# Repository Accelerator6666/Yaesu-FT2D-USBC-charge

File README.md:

# FT2D USB-C PD 外接电源适配器（工程评审版）

为 Yaesu FT2DR / FT2DE 手持电台设计的 USB-C PD 转外接直流电源原型工程，使用 KiCad 10。**本工程尚未完成量产前的电气、PCB 和实物验证，请勿直接投板后连接电台。**

## 优先推进：Rev P 低成本模块＋洞洞板路线（2026-10-26）

由于嘉立创 SMT 报价较高，现新增**不依赖 PCB 打板和 SMT 代贴**的 [Rev P 模块／洞洞板试验方案](prototypes/Rev_P_Perfboard/README.md)。用户提供的 **TA3005U 产品参数截图**显示 C1/C2 支持 **12 V / 3 A**，故**优先使用 12 V PD 直通方案**，无需降压模块：参见 [采购与装配清单](prototypes/Rev_P_Perfboard/PROCUREMENT_REV_PD.md)、[12 V 直通接线图](prototypes/Rev_P_Perfboard/wiring_12v_direct.svg) 和 [直通台架放行清单](prototypes/Rev_P_Perfboard/TEST_PLAN_12V_DIRECT.md)。原 [20 V→12 V 降压备选接线图](prototypes/Rev_P_Perfboard/wiring.svg) 与 [测试方案](prototypes/Rev_P_Perfboard/TEST_PLAN.md) 保留以备直通 3 A 动态能力不足时使用。两条路径均需**独立 OVP、保险丝及 E-DC-6 极性核对**。**当前仅完成设计和规格截图核对，尚未购买和实测，严禁直接接电台。**

Rev B 作为后续小型化 PCB 参考版本原样保留；此前嘉立创 **5 片 PCB 待付款订单**不受本次设计文件影响，本项目没有操作付款或撤单。

**最新进展（2026-10-26）：** [PCB Rev B 工作版](hardware/Rev_B/README.md) 已更换 J1 为 HRO `TYPE-C-31-M-12`（JLC **C165948**）、L1 为 JIERR `SRG1260-100-M`（**C53463013**），并完成接地回流修复、局部 1.6–2.0 mm 目标功率铜皮、重新填铜。C18 已采用 Panasonic `EEH-ZA1V470P`（**C178639**）的匹配 6.3 mm 焊盘作为候选，取代原 5 mm 焊盘型号，仍须核定温度等级。**本轮 U3 新增 4 颗标准功率过孔和 In2 两个独立局部宽铜岛；C26 从 100 nF 升级为 2.2 µF/25 V X7R 候选（C415535），0603 焊盘不变。** 更新后 KiCad 10.0.7 **ERC 0 / DRC 违规 0 / 未连接 0 / 原理图对照 0**，3 A 温升仍未签核。

嘉立创用的 [BOM/CPL 原生导出及 SMT 供料评审](manufacturing/Rev_B/README.md) 已更新到 **57 行原生 BOM / 53 个实际 SMT 坐标 / 53 个候选 JLC 物料号（37 种料）**；候选 JLC 四列 BOM、五列 CPL 与逐项来源追溯表都在 `REVIEW_ONLY_NOT_FOR_FAB`，并已通过 53/53 本地 BOM/CPL 位号和坐标审计。**R22 已由 101 kΩ 兼容改值为 102 kΩ（JLC SMT C861068），OVLO 标称值相应提高约 0.12 V，工厂实时库存仍需确认。4 层 Gerber、焊膏、钻孔已随本轮源工程重新导出。** 另新增 [嘉立创报价/贴片在线预览三件套](manufacturing/Rev_B/QUOTE_PREVIEW_ONLY_NOT_RELEASED/README_FIRST.md)：平铺 Gerber+钻孔 ZIP、53 位号 BOM 和 CPL，可以立即上传**预览/询价**，仍不能直接确认订单。同步生成了 [U3 3A 铜线保守损耗估算](manufacturing/Rev_B/PREFLIGHT/power_path_screening.json) 和 [STUSB4500 NVM/首板上电方案](manufacturing/Rev_B/PD_NVM_AND_FIRST_POWER_ON_PLAN.md)。尤其注意 STUSB4500 **出厂 20V PDO 只有 1A，且默认 5V 时可使能电源路径**，必须在首板测试前重新配置并验证。**当前仍 NO-GO，不要直接下单**：待完成 3 A 电热及 Buck 回路复核、全部候选元件真实 SMT 供货/兼容性确认、JLC 贴片预览和工程签核。正式放行脚本继续拦截未签核订单；原始评审 PCB 的 [基线检查](FAB_READINESS.md) 保留。

## 原 Rev B 集成 PCB 的目标参数（不适用于 Rev P-D 直通版）

| 项目 | 规格 |
| --- | --- |
| 输入 | USB-C PD 固定 20 V / ≥3 A（至少 60 W） |
| 输出 | 标称 12.5 V / 连续 3 A（37.5 W） |
| 设备端 | Yaesu E-DC-6 兼容尾线，使用前必须核对极性和尺寸 |
| 主控制器 | STUSB4500QTR（PD 协商）、LM61460-Q1（同步降压）、TPS259474A（eFuse） |
| PCB | 四层，含初始原型布局与自动布线评审版 |

FT2D 的电池充电由电台内部管理；此工程**不是**独立的锂电池充电器。

## 文件索引

- `FT2D_PD20V_12V5_3A_评审原理图.kicad_sch`：KiCad 原理图。
- `FT2D_PD20V_12V5_3A_评审原理图.kicad_pcb`：已导入自动布线的评审 PCB。
- `FT2D_PD20V_12V5_3A_原型板.kicad_pcb`：早期原型板布局版本。
- 两份 `.kicad_pro`：各自的工程设置；`.kicad_prl` 属于本地用户界面状态，没有纳入版本控制。
- `FT2D.kicad_sym`、`FT2D.pretty/`、`sym-lib-table`、`fp-lib-table`：自定义符号和封装库。
- `FT2D_PD20V_12V5_3A_BOM.csv`：元件清单。
- `FT2D_PD20V_12V5_3A_评审原理图.pdf`、`FT2D_PD20V_12V5_3A_评审.net`：评审导出资料。
- `FT2D_USB-C_PD_3A_设计说明.md`、`FT2D_PD20V_12V5_3A_原理图连接表.md`：设计要求、连接表及测试计划。
- `FT2D_PD20V_12V5_3A_ERC.txt`：提供的 ERC 检查记录（0 errors / 0 warnings；不能替代板级验证）。
- `generate_schematic.py`、`generate_pcb.py`、`make_footprints.py`、`postprocess_route.py`：设计辅助脚本。

## 打开方式

1. 安装 KiCad 10，下载或克隆本仓库。
2. **当前工作版**：打开 `hardware/Rev_B/FT2D_PD20V_12V5_3A_评审原理图.kicad_pro`，对应 `.kicad_sch` 和 `.kicad_pcb`；原始根目录文件保留为此前的评审基线。
3. `hardware/Rev_B/README.md` 有当前实际检查结果；`manufacturing/Rev_B/` 有不可投板的供料/CPL 预览与放行门禁。
4. 如需重新生成自定义封装，运行 `python make_footprints.py`。仓库已包含脚本生成的七个自定义封装。

部分其他自动生成脚本含有原开发环境的本地路径以及未附带的临时网络表输入，**不是**开箱即用的跨平台构建流程；直接阅读和编辑现有 KiCad 文件不依赖运行这些脚本。

## 投板与上机前必须确认

- 按厂家数据手册复核所有芯片、USB-C 连接器及自定义封装的引脚、焊盘和焊膏开窗。
- 重新运行 ERC / DRC、检查所有连接与四层铜皮，审查 Gerber / 钻孔。
- **Rev B 虽已有 1.6–2.0 mm 目标宽度的局部功率铜皮，但受限处仍有 0.3–0.6 mm 细颈，不等于全路径可连续承载 3 A。**需要完成电流通道截面、过孔与温升签核。
- 正确烧录、读回并验证 STUSB4500 NVM 的 PD 请求参数，确认非 20 V / 3 A 电源不会向电台供电。
- 不接 FT2D，先用电子负载验证输出电压、纹波、温升、负载阶跃、短路、过流、过压以及射频噪声影响。
- 实测电台端插头的正负极、机械匹配与满载电压后，才考虑连接真机。

更完整的参数和验收流程参见两份中文设计说明文档。当前工程没有提供足以证明安全可投板或已完成实测的资料。

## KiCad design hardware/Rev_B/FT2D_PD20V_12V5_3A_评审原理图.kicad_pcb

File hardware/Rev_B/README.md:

# FT2D PCB Rev B（JLCPCB 首板工作版，未放行）

检查日期：2026-10-26；KiCad 10.0.7；目标板厂：嘉立创 JLCPCB；目标工艺：4 层 PCB + SMT 代贴片。

> **规则检查已清零，但制造仍 NO-GO。** 本目录可在 KiCad 10 打开；J1/L1 换料、C18 新候选的焊盘调整、GND 回流布线、局部功率铜、U3 四颗标准过孔及 In2 两个局部功率铜岛均已同步，全部 DRC/Parity 通过。**53/53 个 SMT 位号已匹配候选 LCSC 编码，37 种物料均未正式获批**。剩余 3 A 功率/散热审查、JLC 实际供料/兼容性、元器件和装配方向签核尚不能省略。

## 当前可复现检查

```sh
kicad-cli sch erc --format json -o erc_rev_b.json FT2D_PD20V_12V5_3A_评审原理图.kicad_sch
kicad-cli pcb drc --schematic-parity --refill-zones --format json -o drc_rev_b.json FT2D_PD20V_12V5_3A_评审原理图.kicad_pcb
```

| 检查 | 实际结果 | 说明 |
| --- | --- | --- |
| 原理图 ERC | **0** | 仅表示静态 ERC 通过 |
| 异网短路 / 铜间距违规 | **0** | KiCad 本次静态规则检查未发现硬性违规 |
| DRC violations | **0** | U1 已用系统库相同 29 焊盘封装刷新；局部无效热焊盘连接已处理 |
| DRC unconnected | **0** | 独立顶层 GND 区域通过常规穿孔过孔与内层地面连接，C5 补上局部 GND 逃线 |
| schematic parity | **0** | PCB 与当前 Rev B 原理图一致；DNP 设置同步 |

上述结果按此目录所附 `erc_rev_b.json` 和 `drc_rev_b.json` 为准。**规则检查 0/0/0/0 不是 3 A 载流能力、PD 功能、贴片方向或安全性能的认证。**

## 本轮已核对并替换的 JLC 物料

| 位号 | 新器件及嘉立创料号 | 原厂/焊盘验证 | 装配保留事项 |
| --- | --- | --- | --- |
| **J1** | HRO `TYPE-C-31-M-12`，**C165948** | 标称 **20 V / 5 A**；KiCad 10 标准 `Connector_USB:USB_C_Receptacle_HRO_TYPE-C-31-M-12`；按产品引脚表保持 CC1/CC2、VBUS、GND 网络，中心 `(24.15,42)`，转角 `-90°` | 立创标为 SMT，但带 **4 个穿孔屏蔽固定脚**；必须由 JLC 订单预览确认这种混合结构可贴装及固定脚焊接方式，并确认板边插拔可达性 |
| **L1** | JIERR `SRG1260-100-M`，**C53463013** | **10 µH ±20%**，Isat **14 A typ**，Idc **11 A typ**，DCR **25 mΩ max**；原厂落地尺寸 14.6 mm 总跨距、7.4 mm 焊盘间隙、4.8 mm 焊盘高度，生成 `FT2D:JIERR_SRG1260_100M`；器件高度 **6 mm max** | 数据表只是额定能力，不是开关纹波/温升实测；尤其要确认电台安装净高 |
| **C18** | Panasonic `EEH-ZA1V470P`，**C178639** | 35 V / 47 µF 混合铝电容，**60 mΩ @100 kHz、1.3 A @100 kHz**；与原 EEH-ZL1V470R 的 **60 mΩ** 指标一致；PCB/C18 的封装改为 KiCad `CP_Elec_6.3x5.8`，中心由 `(62,48)` 移至 `(61.5,48)`，保持 pad 1=`/VBUS_SW`、pad 2=`/GND`；替代后 ERC 0、DRC 0、Parity 0 | **温度由原 135°C 降为 105°C**（虽是 10000 h @105°C）；须复核实际环境和热裕量、极性、焊盘尺寸及库存；不能据此自动批准 SMT |

J1 原厂 [PDF](https://datasheet.lcsc.com/datasheet/pdf/9e56b777c022540fcce7c7f67825f55e.pdf?productCode=C165948)，L1 原厂 [PDF](https://datasheet.lcsc.com/datasheet/pdf/970397481256e0f4304d2971057c0f55.pdf?productCode=C53463013)。立创供料库存会变化，投单时须再次确认。

## 主要阻止打板的问题（按优先级）

1. **3 A 功率铜尚未签核**：顶层沿 `/USB_VBUS`、`/VBUS_RAW`、`/VBUS_SW`、`/SW`、`/V12P5`、`/VOUT` 增加 **1.6–2.0 mm 目标宽度**的合并局部铜皮，但异网净距会裁切狭颈；原细线最小仍为 **0.25–0.60 mm**。本轮按照 TI eFuse IN/OUT 加铜和散热过孔建议，在 `In2.Cu` 增加 `/V12P5` **51.54 mm²** 和 `/VOUT` **55.29 mm²** 互不接触的局部铜岛，每网两颗 **0.6/0.3 mm 普通过孔**；两岛均连续并通过 DRC。U3 Pin 5/6 仍存在约 **0.3 mm** 短逃线，**不能宣称全线按 3 A 等效宽度连通**。需复查各路径最窄断面、过孔电流、内层地回流、压降与满载升温。
2. **BUCK 高频布局仍待复核**：U2 `(79,43)`，L1 SW 端 `(83.5,43)`，直距约 **3.7 mm**；输入 C12/C13 高频去耦位置、U2 VIN/PGND 回路、输出电容接地/反馈 Kelvin 路径都须按照 TI 指南审查，SW 追踪铜面积仍可能引入 EMI。
3. **JLC 候选编码齐备，采购/装配未签核**：53 个非 DNP SMT 位号已有 37 个候选 C-code，本地 BOM/CPL 静态比对全通过。**这不等于 JLC SMT 供料实时有货、同外形即可直接替代，或可下单**。F1 `C41342`、C18 `C178639`、C23 `C46550464` 温度/ESR 降额需确认；**R22 已由 101 kΩ 改为嘉立创标注 SMT 的 102 kΩ / `C861068`**，OVLO 标称阈值约从 13.32 V 变为 13.44 V，实际误差/瞬态仍须验证；**C26 已从 100 nF/25 V 改为 2.2 µF/25 V/0603 X7R 候选 `C415535`，但实际 12.5 V DC bias 后容值需核对**；其他 1210 MLCC 需核实 DC 偏压有效电容，0.1% 电阻需复核实际规格；J1 混合 SMT/通孔固定脚需要装配商确认。
4. **SMT 机器贴装仍未确认**：53 个位置与 PCB 坐标已通过本地审计，但 HRO J1 `-90°`、异形功率器件方向、极性电容、贴片取放中心及 KiCad Y 轴符号必须在 JLC 预览中人工核对。
5. **功能级风险**：STUSB4500 NVM 需编程并验 20 V PDO；eFuse 限流、DC-DC 环路、输出线束电台端极性、热和射频噪声尚无实测。

**新增定量初筛（仍未签核）**：按照 PCB 当前 U3 Pad 5/6 和 35 µm 标称顶铜，假设整段 0.2998 mm 原走线独自承载 3A，分别在 90°C 得到约 **54 mW（2.85 mm 输入）/28 mW（1.49 mm 输出）**的铜阻损耗模型值；实际上 pad 与同网铜区有重叠和并联，若实板铜厚偏低或温度更高损耗还会增加，此算法不能计算温升。U3 典型 28.3mΩ R_ON 在 3A 下自身耗散约 **0.255W**，R26=820Ω 按 TI 典型公式电流门限约 **4.07A**，必须用热测、过流试验核查。自动初筛脚本 `../../engineering_tools/screen_rev_b_power_path.py` 以及结果 `../../manufacturing/Rev_B/PREFLIGHT/power_path_screening.json` 可复现。**STUSB4500 出厂 PDO3=20V/1A，且 `POWER_ONLY_ABOVE_5V=0`，不是本项目所需 20V/3A**；详见 `../../manufacturing/Rev_B/PD_NVM_AND_FIRST_POWER_ON_PLAN.md`。可先使用 `../../manufacturing/Rev_B/QUOTE_PREVIEW_ONLY_NOT_RELEASED/` 作 JLC 在线报价/贴装预览，**不可当作正式放行**。

## 已完成的布线/设计动作

- 原评审 PCB 不变；此目录保留 Rev B 的独立原理图、PCB、工程设置和封装库。
- 保持 `POWER_REV_B` netclass 0.6 mm 路由过渡值，同时用 `power_pours_rev_b.py` 增加局部宽铜；**铜宽仍需实体连续性和发热签核**。
- 用两个新物料封装替换 J1/L1，并将 U2 SW 与 L1 SW 缩至约 3.7 mm；全部原走线重建并验证无异网硬短路。
- 已修复 U1 KiCad 系统库封装不一致告警；优先以常规 **0.6/0.3 mm GND 穿孔过孔**保留回流通路，再全板重布线。U1/U2/R25/R26 周边地与 C5 局部地均已接通，未使用未签核的焊盘盲埋孔。GND 特殊热焊盘局部改为实体连接；全板 DRC **0 违规 / 0 未连接**。
- 把两段自动布线占用 `In1.Cu` GND 参考面的 `/VBUS_SW` 导线转到 `In2.Cu`，避免在 Buck 下方切割连续地平面；重新填铜验证 0/0。
- C18 替换候选 Panasonic C178639 的直径更大，PCB/原理图/符号库同步换成 6.3×5.8 mm 封装，左移 0.5 mm 消除 `/BUCK_VCC` 净距冲突；极性和所有静态规则再次通过。**105°C 温度等级待确认**。
- U3 TPS259474A 的 `/V12P5` 和 `/VOUT` 各加 2 颗常规 0.6/0.3 mm 穿孔并连入 In2 局部功率铜皮（`add_u3_power_stitch_rev_b.py`）；分别提供约 **51.54 / 55.29 mm²** 内层扩散面积，远离现有 In1 模拟反馈/ILM 走线，局部形状/孔距经隔离试板迭代到 DRC0。**新增铜不等于已完成 3 A 温升/EMI 验证。**
- 根据 TI TPS25947 的 OUT 端建议把 **C26 从 100 nF/25 V 升级为 2.2 µF/25 V X7R 0603**，Murata 候选 `GRM188Z71E225KE43D` / `C415535`，原 PCB 0603 pad 保持不变，原理图/符号库/原生 BOM/JLC 候选清单同步；偏压有效容值和取放/库存待审。
- **修复贴片坐标漏项**：将 L1、Q1、U2、U3、D1 自定义封装标为 `attr smd`；C11/R14 DNP 排除，实际预览 CPL 为 **53 个位置**。
- 原理图和 PCB 的 DNP 与 BOM 属性一致，PD 协商和电台输出的电气定义未修改。

可审计工具在 `../../engineering_tools/`；未通过 DRC 的局部接地布线实验已从 PCB 与提交文件中移除。

## 投板门槛

- [ ] 全面优化 U2–L1–电容功率环路，宽铜/铜皮与热设计通过工程复核。
- [x] ERC 0、DRC 0 实质违规、**DRC 0 未连接**、Parity 0（KiCad 10.0.7）；工程复查仍另计。
- [ ] U1、U2、U3、Q1、J1、L1 的封装与厂家 land pattern 对照签核。
- [x] **候选** JLC/LCSC 料号覆盖 53/53 SMT 位号；DNP C11/R14、人工工序 J2/J3 不入 SMT BOM/CPL；本地 BOM/CPL 结构检查通过。
- [ ] 53/53 候选编码逐项确认 JLC 实时 SMT 可贴装/有货、原厂物料与焊盘匹配；在线 SMT 预览方向及极性正确，才能生成 `BOM_APPROVED.csv` / `CPL_APPROVED.csv`。
- [ ] PD NVM 烧录工装、12.5V 无电台电子负载测试计划完备。

`../../manufacturing/Rev_B/REVIEW_ONLY_NOT_FOR_FAB/` 提供 **57 行原生 BOM、53 行 CPL、53 行候选 JLC BOM/坐标、供料追溯表、供料工作簿、顶层/In2 铜预览图和随本轮板文件重新导出的全部 Gerber/Excellon 钻孔 QA 文件**，这些均是**审阅版，不能直接下单**。`export_jlcpcb_release_rev_b.sh` 的静态检查已通过，但正确地停在**没有完整签核 BOM/CPL/工程签字**的下一道门禁。**正式 RELEASE_READY 制造包未生成。**

## 关键一手资料

- [JLCPCB KiCad 10 BOM / Pick-and-Place 指南](https://jlcpcb.com/help/article/how-to-generate-the-bom-and-centroid-file-from-kicad)
- [ST STUSB4500](https://www.st.com/resource/en/datasheet/stusb4500.pdf)
- [TI LM61460-Q1](https://www.ti.com/lit/ds/symlink/lm61460-q1.pdf)
- [TI TPS25947](https://www.ti.com/lit/ds/symlink/tps25947.pdf)

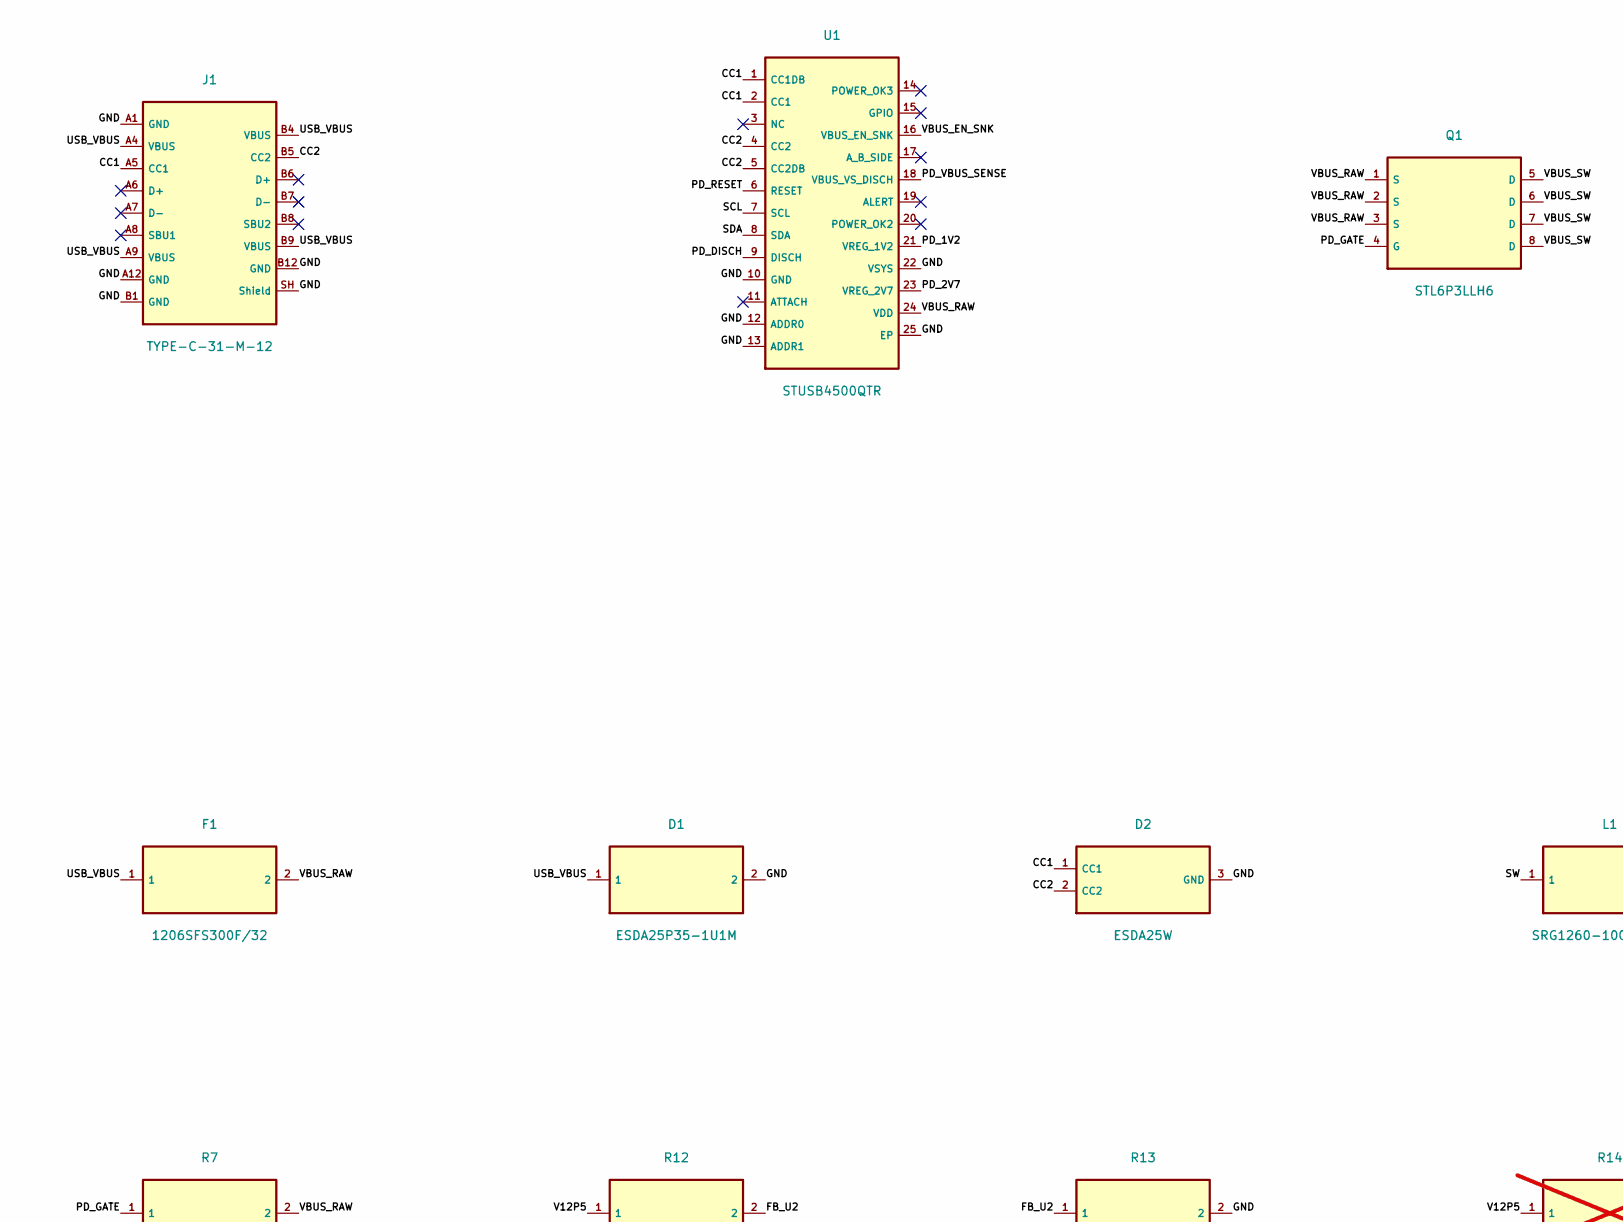
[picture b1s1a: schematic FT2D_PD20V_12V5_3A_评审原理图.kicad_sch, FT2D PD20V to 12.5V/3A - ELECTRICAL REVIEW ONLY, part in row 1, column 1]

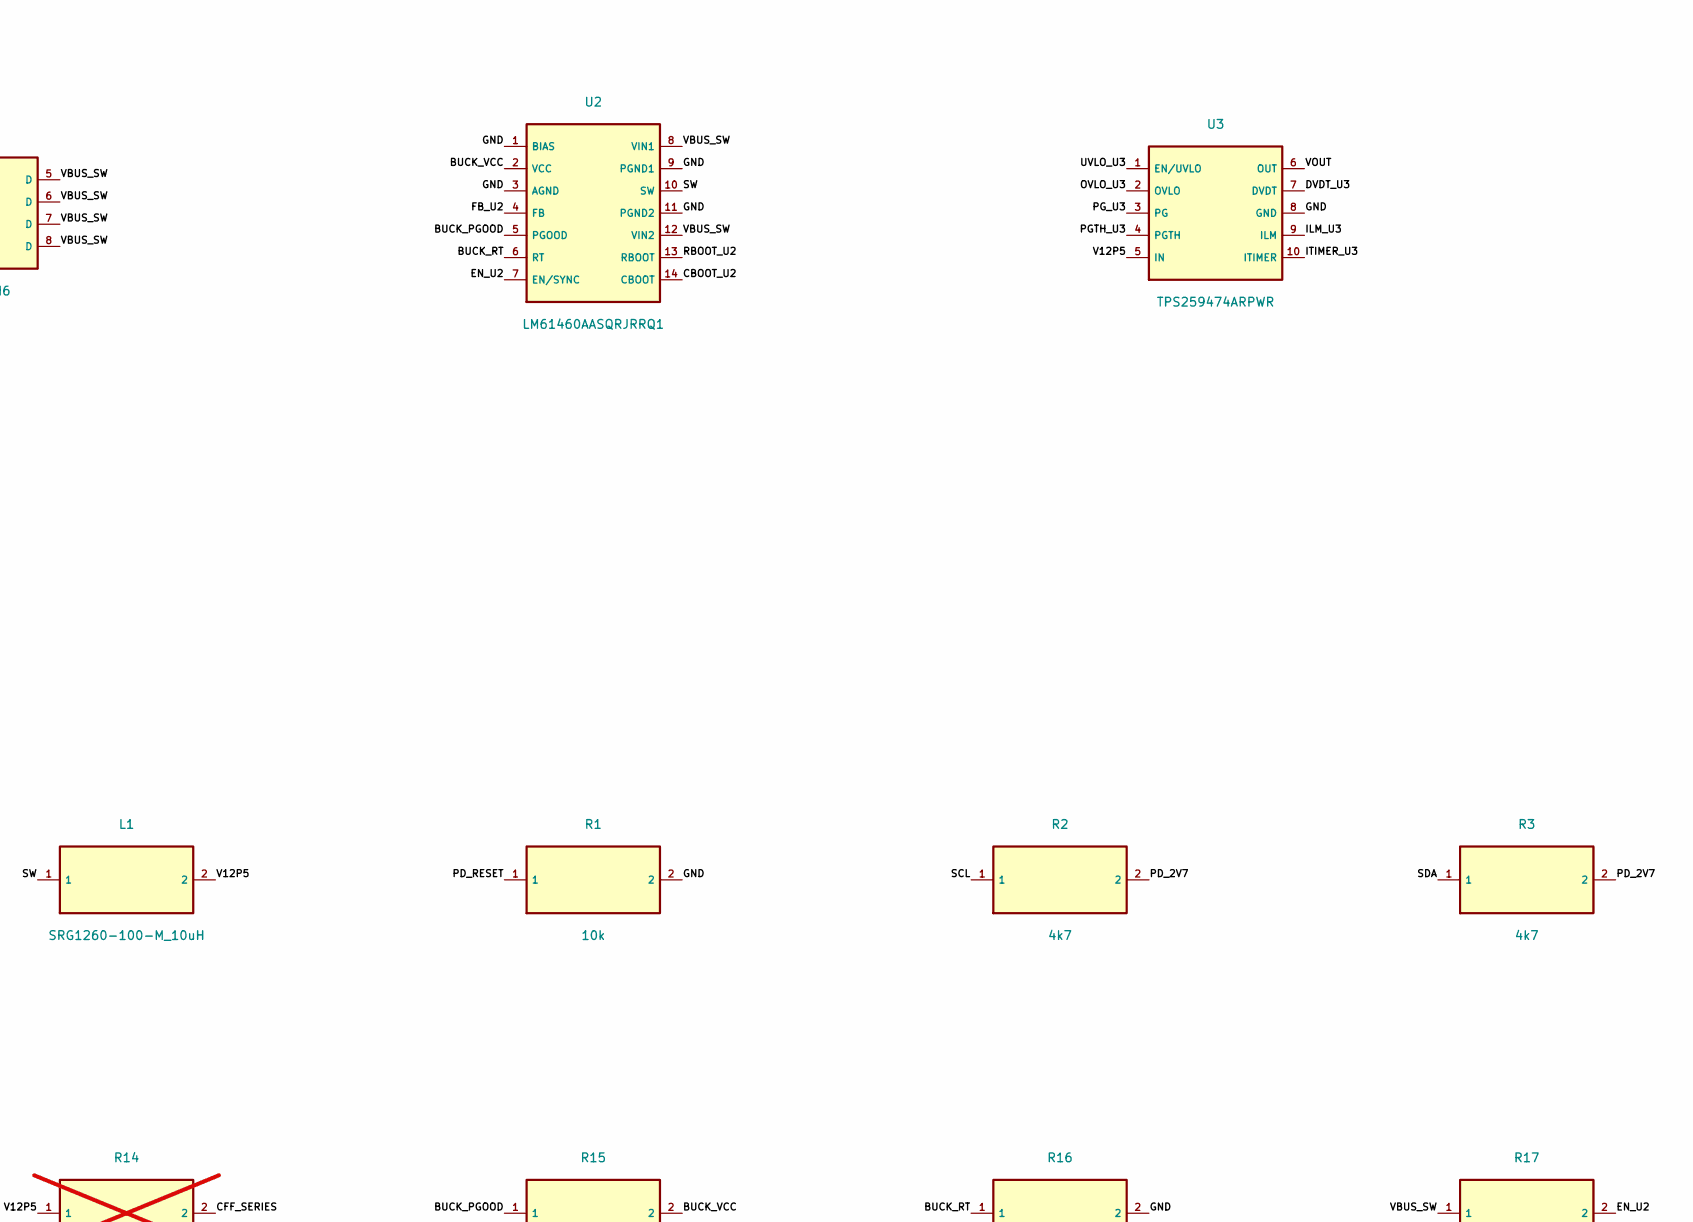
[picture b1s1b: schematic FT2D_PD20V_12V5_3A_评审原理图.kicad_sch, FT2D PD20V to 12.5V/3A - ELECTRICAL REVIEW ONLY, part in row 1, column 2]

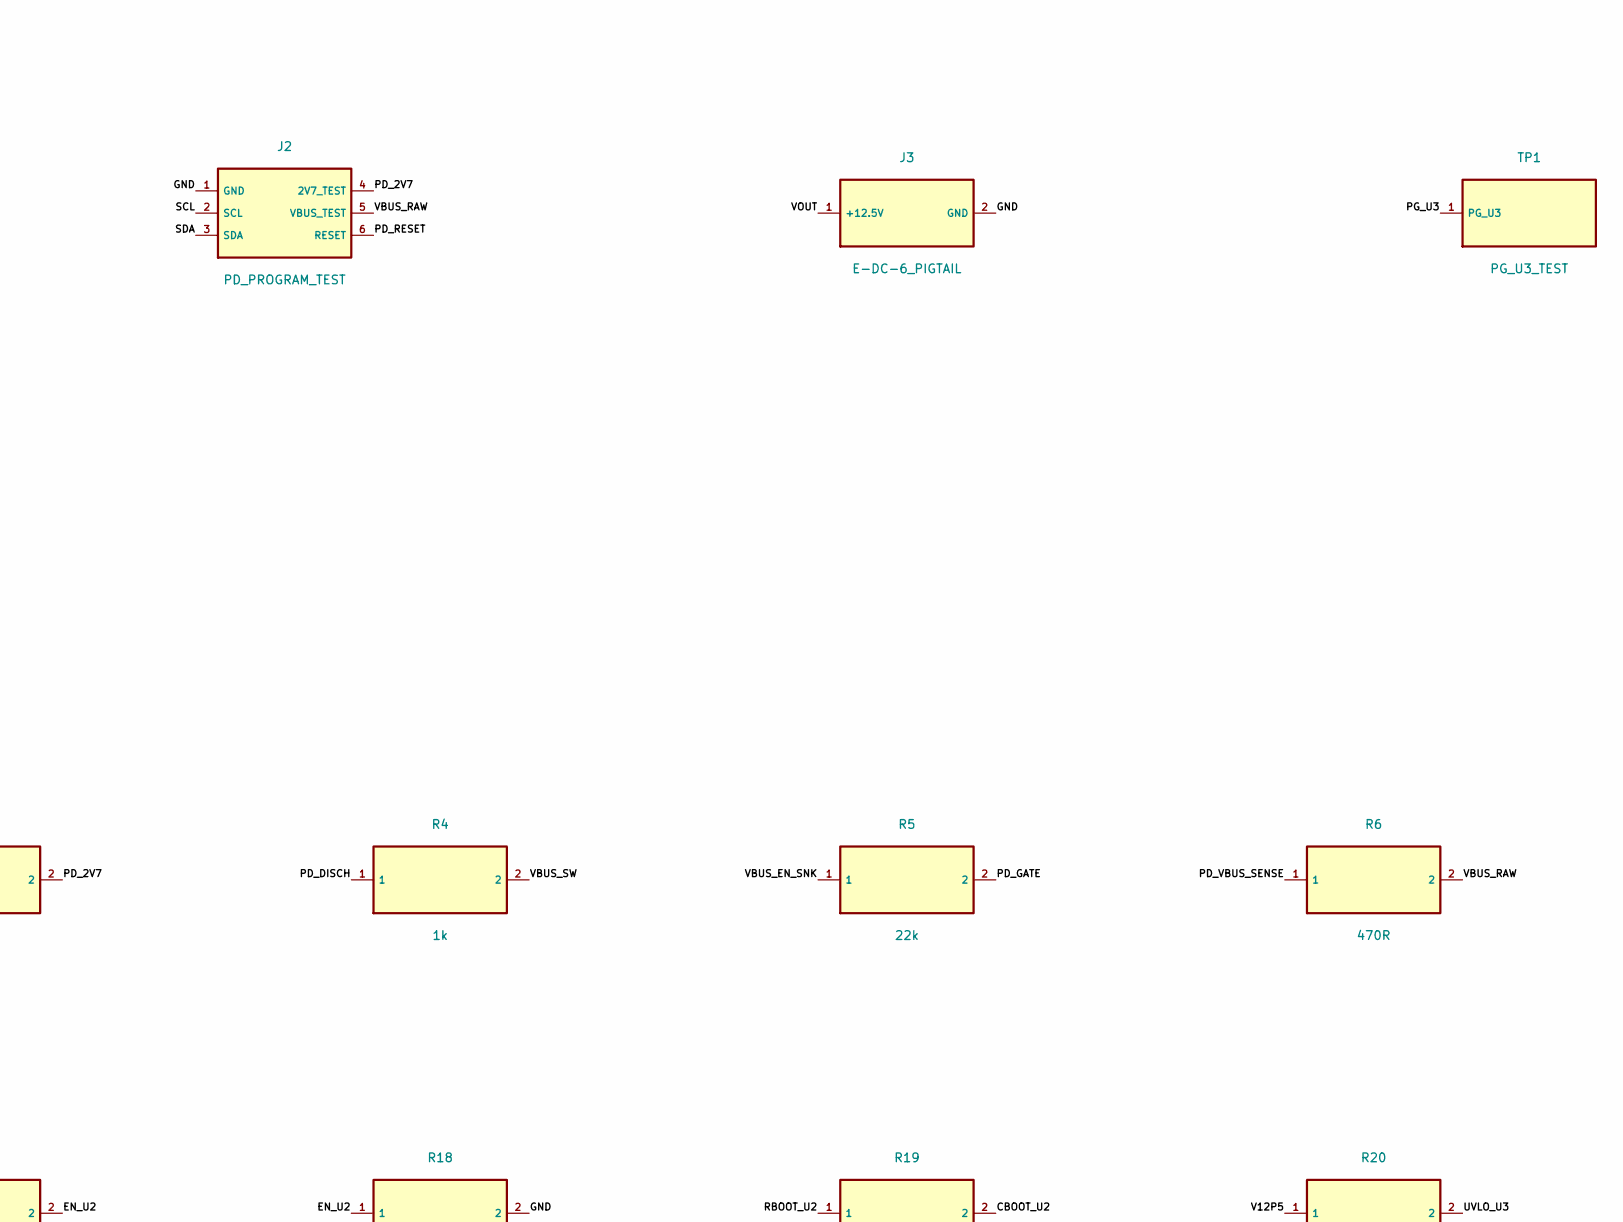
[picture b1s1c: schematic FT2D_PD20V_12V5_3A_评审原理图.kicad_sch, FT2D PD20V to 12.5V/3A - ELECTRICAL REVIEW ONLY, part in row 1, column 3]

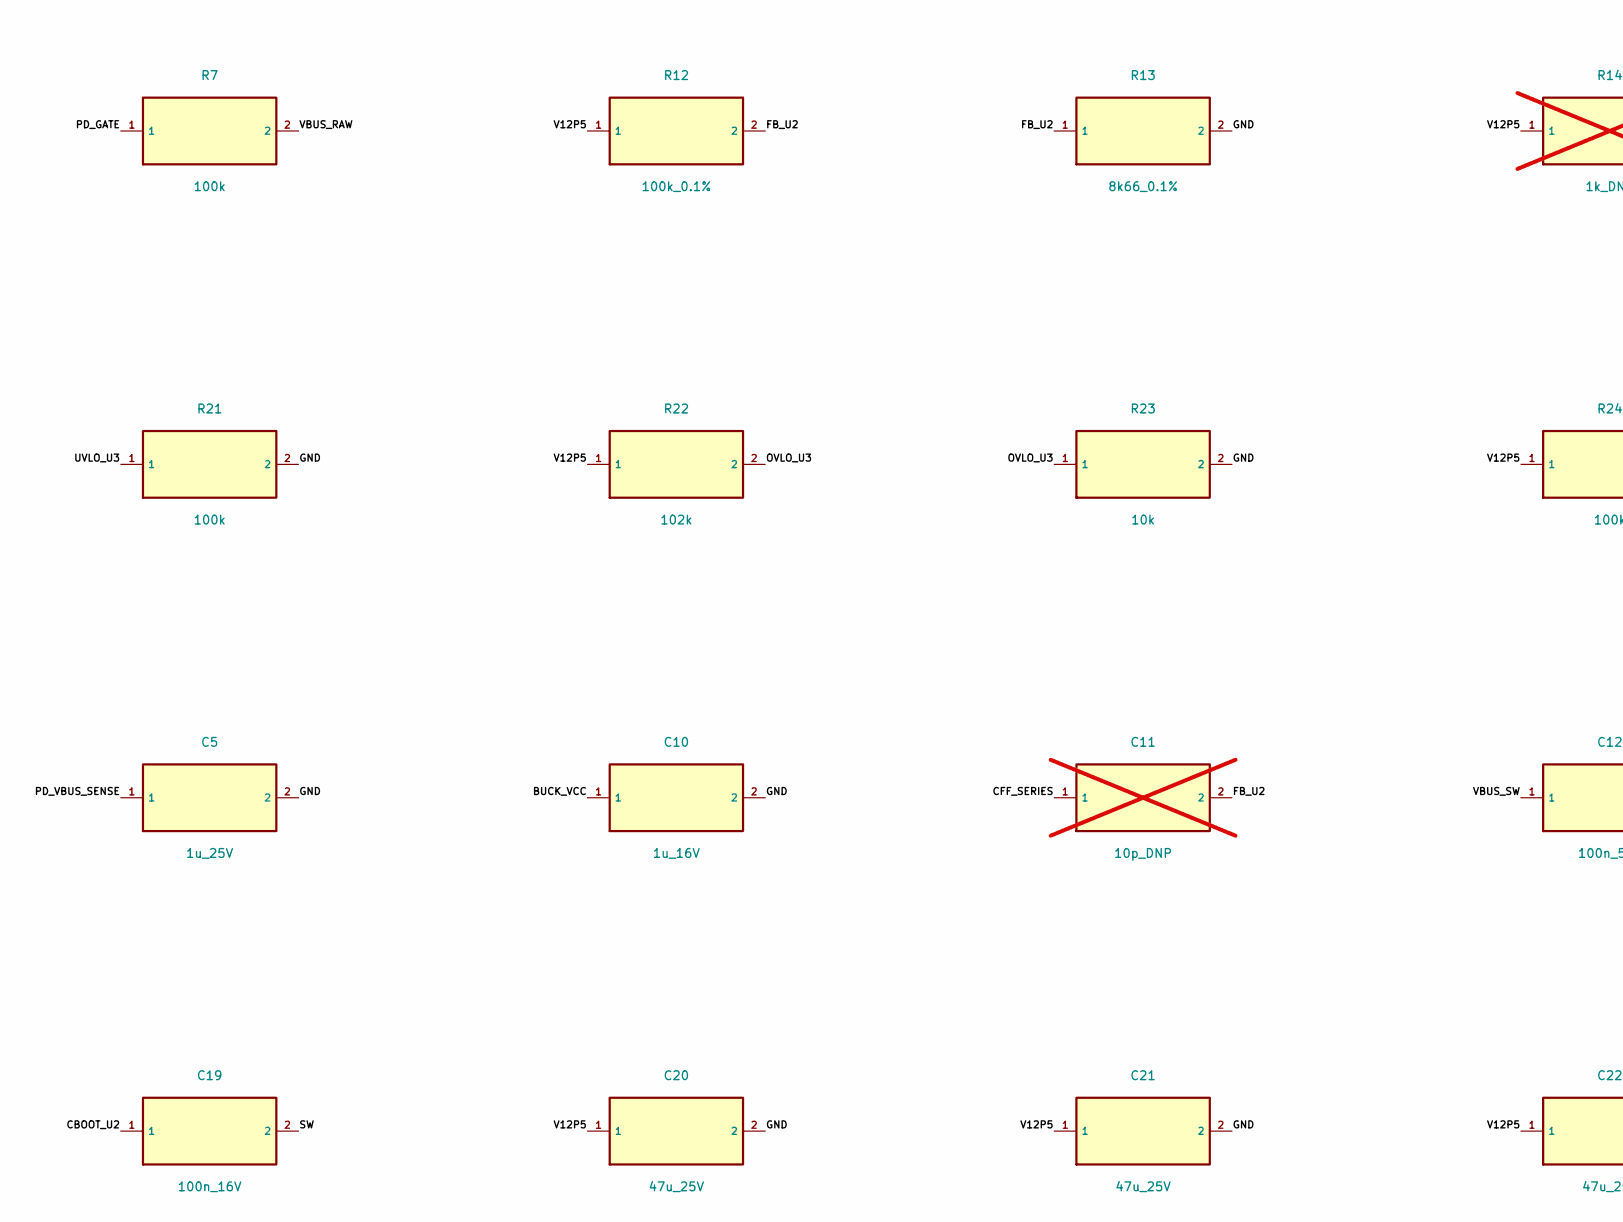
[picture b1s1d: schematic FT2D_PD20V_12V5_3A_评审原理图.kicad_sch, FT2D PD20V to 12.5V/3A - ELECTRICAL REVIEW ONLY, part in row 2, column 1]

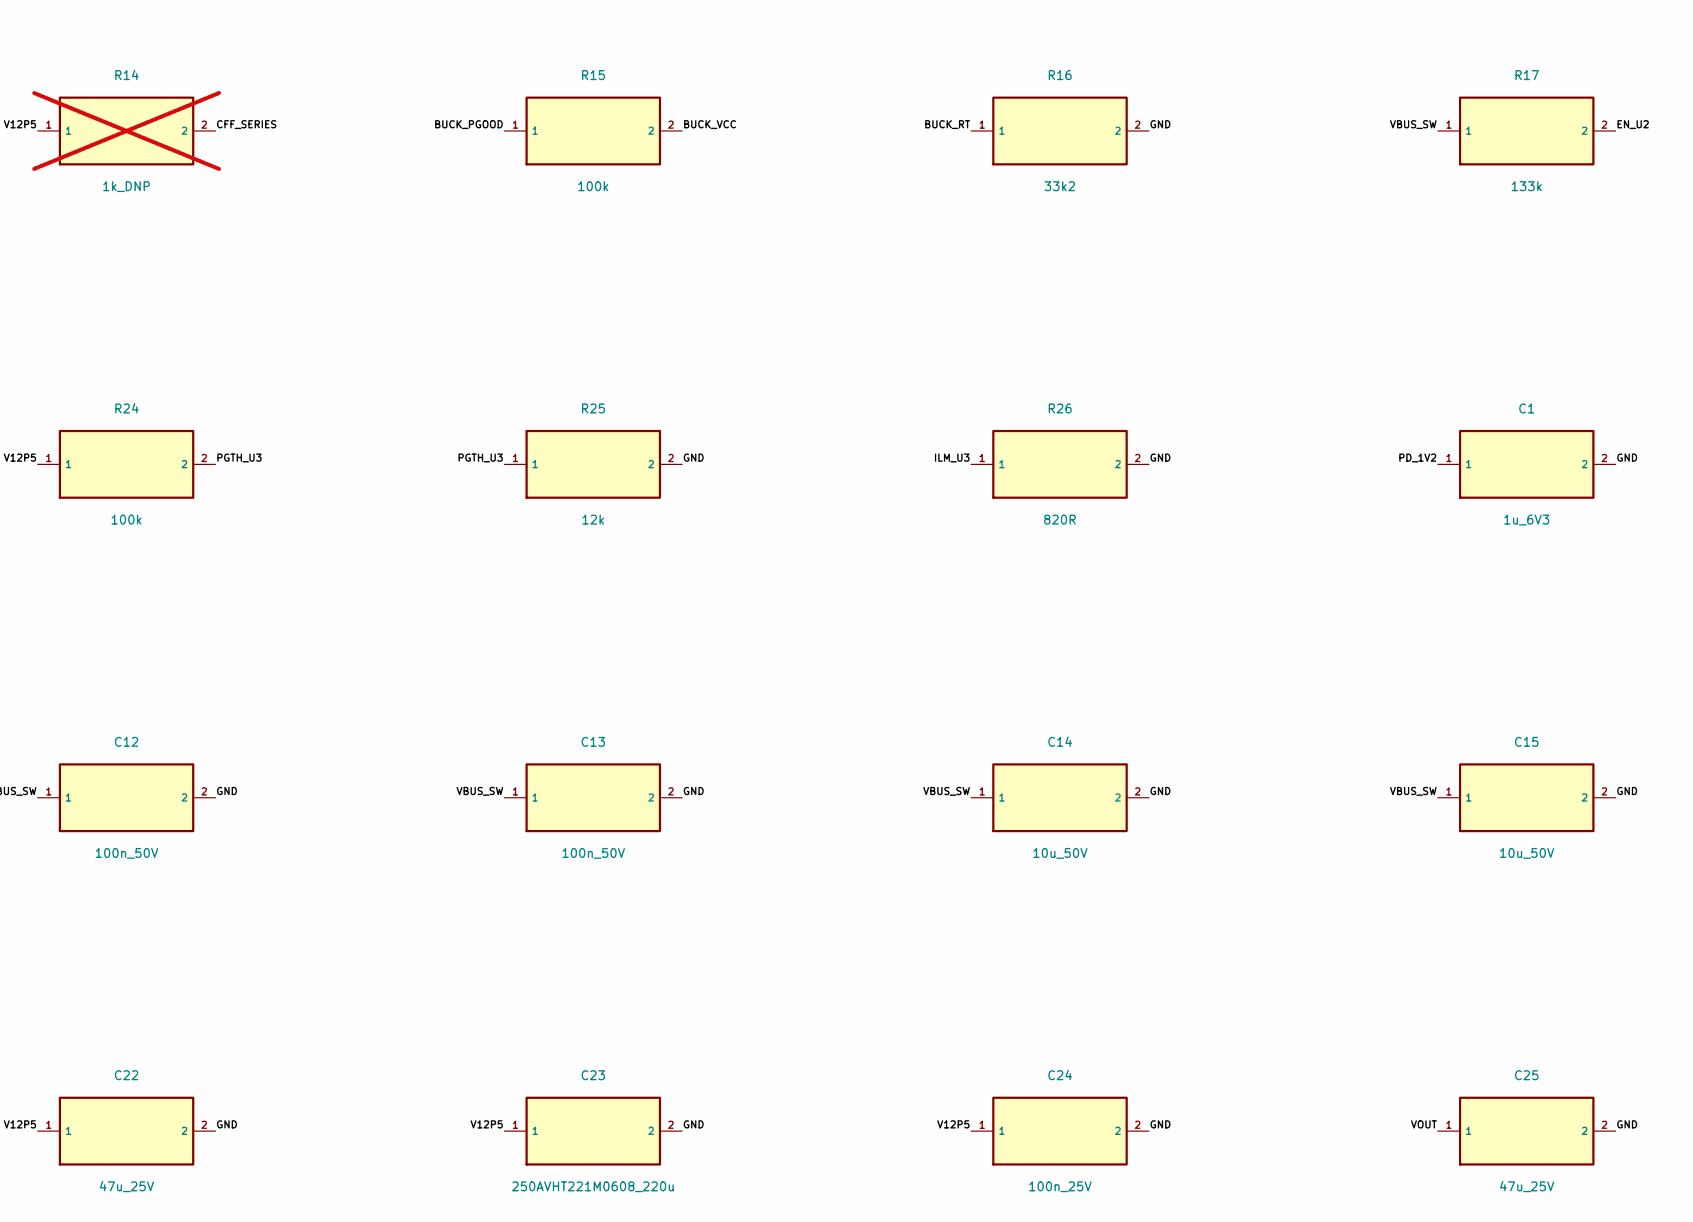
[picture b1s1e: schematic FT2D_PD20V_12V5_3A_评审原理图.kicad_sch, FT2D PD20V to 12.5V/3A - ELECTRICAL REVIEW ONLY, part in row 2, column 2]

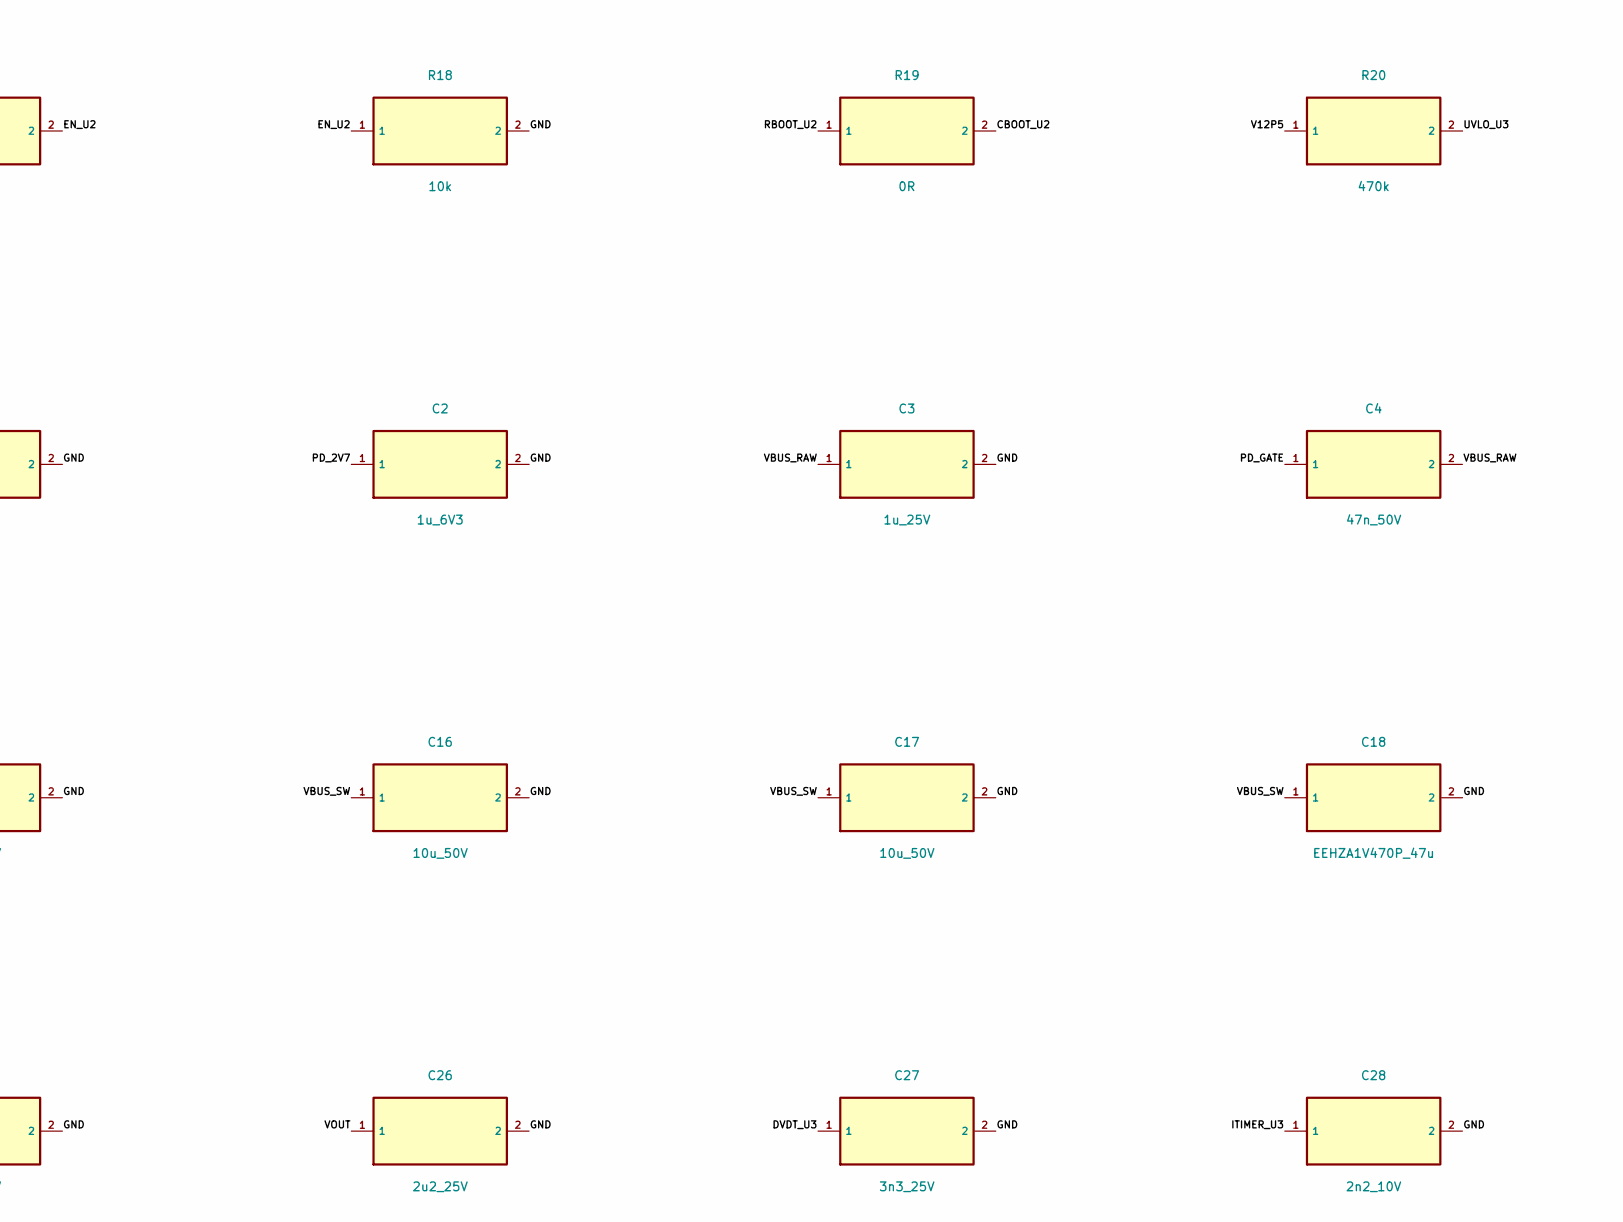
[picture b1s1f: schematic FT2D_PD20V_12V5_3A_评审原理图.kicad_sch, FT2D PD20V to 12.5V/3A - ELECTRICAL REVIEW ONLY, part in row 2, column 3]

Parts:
C1, C2: 1u_6V3; C_0603_1608Metric
C3, C5: 1u_25V; C_0805_2012Metric
C4: 47n_50V; C_0603_1608Metric
C10: 1u_16V; C_0603_1608Metric
C11: 10p_DNP; C_0603_1608Metric; not fitted
C12, C13: 100n_50V; C_0603_1608Metric
C14, C15, C16, C17: 10u_50V; C_1210_3225Metric
C18: EEHZA1V470P_47u; CP_Elec_6.3x5.8
C19: 100n_16V; C_0603_1608Metric
C20, C21, C22, C25: 47u_25V; C_1210_3225Metric
C23: 250AVHT221M0608_220u; CP_Elec_6.3x7.7
C24: 100n_25V; C_0603_1608Metric
C26: 2u2_25V; C_0603_1608Metric
C27: 3n3_25V; C_0603_1608Metric
C28: 2n2_10V; C_0603_1608Metric
D1: ESDA25P35-1U1M; ST_ESDA25P35_1U1M
D2: ESDA25W; SOT-323_SC-70
F1: 1206SFS300F/32; Fuse_1206_3216Metric
J1: TYPE-C-31-M-12; USB_C_Receptacle_HRO_TYPE-C-31-M-12
J2: PD_PROGRAM_TEST; PD_Programming_Pads_1x06_P2p54
J3: E-DC-6_PIGTAIL; Wire_Pads_2x_P3mm
L1: SRG1260-100-M_10uH; JIERR_SRG1260_100M
Q1: STL6P3LLH6; ST_PowerFLAT_3p3_TypeF
R1, R18, R23: 10k; R_0603_1608Metric
R2, R3: 4k7; R_0603_1608Metric
R4: 1k; R_0603_1608Metric
R5: 22k; R_0603_1608Metric
R6: 470R; R_0603_1608Metric
R7, R15, R21, R24: 100k; R_0603_1608Metric
R12: 100k_0.1%; R_0603_1608Metric
R13: 8k66_0.1%; R_0603_1608Metric
R14: 1k_DNP; R_0603_1608Metric; not fitted
R16: 33k2; R_0603_1608Metric
R17: 133k; R_0603_1608Metric
R19: 0R; R_0603_1608Metric
R20: 470k; R_0603_1608Metric
R22: 102k; R_0603_1608Metric
R25: 12k; R_0603_1608Metric
R26: 820R; R_0603_1608Metric
TP1: PG_U3_TEST; TestPoint_Pad_1.0x1.0mm
U1: STUSB4500QTR; QFN-24-1EP_4x4mm_P0.5mm_EP2.7x2.7mm
U2: LM61460AASQRJRRQ1; TI_RJR0014A
U3: TPS259474ARPWR; TI_RPW0010A

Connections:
/BUCK_PGOOD: R15.1, U2.5 (PGOOD)
/BUCK_RT: R16.1, U2.6 (RT)
/BUCK_VCC: C10.1, R15.2, U2.2 (VCC)
/CBOOT_U2: C19.1, R19.2, U2.14 (CBOOT)
/CC1: D2.1 (CC1), J1.A5 (CC1), U1.1 (CC1DB), U1.2 (CC1)
/CC2: D2.2 (CC2), J1.B5 (CC2), U1.4 (CC2), U1.5 (CC2DB)
/CFF_SERIES: C11.1, R14.2
/DVDT_U3: C27.1, U3.7 (DVDT)
/EN_U2: R17.2, R18.1, U2.7 (EN/SYNC)
/FB_U2: C11.2, R12.2, R13.1, U2.4 (FB)
/GND: C1.2, C2.2, C3.2, C5.2, C10.2, C12.2, C13.2, C14.2, C15.2, C16.2, C17.2, C18.2, C20.2, C21.2, C22.2, C23.2, C24.2, C25.2, C26.2, C27.2, C28.2, D1.2, D2.3 (GND), J1.A1 (GND), J1.A12 (GND), J1.B1 (GND), J1.B12 (GND), J1.SH (Shield), J2.1 (GND), J3.2 (GND), R1.2, R13.2, R16.2, R18.2, R21.2, R23.2, R25.2, R26.2, U1.10 (GND), U1.12 (ADDR0), U1.13 (ADDR1), U1.22 (VSYS), U1.25 (EP), U2.1 (BIAS), U2.3 (AGND), U2.9 (PGND1), U2.11 (PGND2), U3.8 (GND)
/ILM_U3: R26.1, U3.9 (ILM)
/ITIMER_U3: C28.1, U3.10 (ITIMER)
/OVLO_U3: R22.2, R23.1, U3.2 (OVLO)
/PD_1V2: C1.1, U1.21 (VREG_1V2)
/PD_2V7: C2.1, J2.4 (2V7_TEST), R2.2, R3.2, U1.23 (VREG_2V7)
/PD_DISCH: R4.1, U1.9 (DISCH)
/PD_GATE: C4.1, Q1.4 (G), R5.2, R7.1
/PD_RESET: J2.6 (RESET), R1.1, U1.6 (RESET)
/PD_VBUS_SENSE: C5.1, R6.1, U1.18 (VBUS_VS_DISCH)
/PGTH_U3: R24.2, R25.1, U3.4 (PGTH)
/PG_U3: TP1.1, U3.3 (PG)
/RBOOT_U2: R19.1, U2.13 (RBOOT)
/SCL: J2.2 (SCL), R2.1, U1.7 (SCL)
/SDA: J2.3 (SDA), R3.1, U1.8 (SDA)
/SW: C19.2, L1.1, U2.10 (SW)
/USB_VBUS: D1.1, F1.1, J1.A4 (VBUS), J1.A9 (VBUS), J1.B4 (VBUS), J1.B9 (VBUS)
/UVLO_U3: R20.2, R21.1, U3.1 (EN/UVLO)
/V12P5: C20.1, C21.1, C22.1, C23.1, C24.1, L1.2, R12.1, R14.1, R20.1, R22.1, R24.1, U3.5 (IN)
/VBUS_EN_SNK: R5.1, U1.16 (VBUS_EN_SNK)
/VBUS_RAW: C3.1, C4.2, F1.2, J2.5 (VBUS_TEST), Q1.1 (S), Q1.2 (S), Q1.3 (S), R6.2, R7.2, U1.24 (VDD)
/VBUS_SW: C12.1, C13.1, C14.1, C15.1, C16.1, C17.1, C18.1, Q1.5 (D), Q1.6 (D), Q1.7 (D), Q1.8 (D), R4.2, R17.1, U2.8 (VIN1), U2.12 (VIN2)
/VOUT: C25.1, C26.1, J3.1 (+12.5V), U3.6 (OUT)

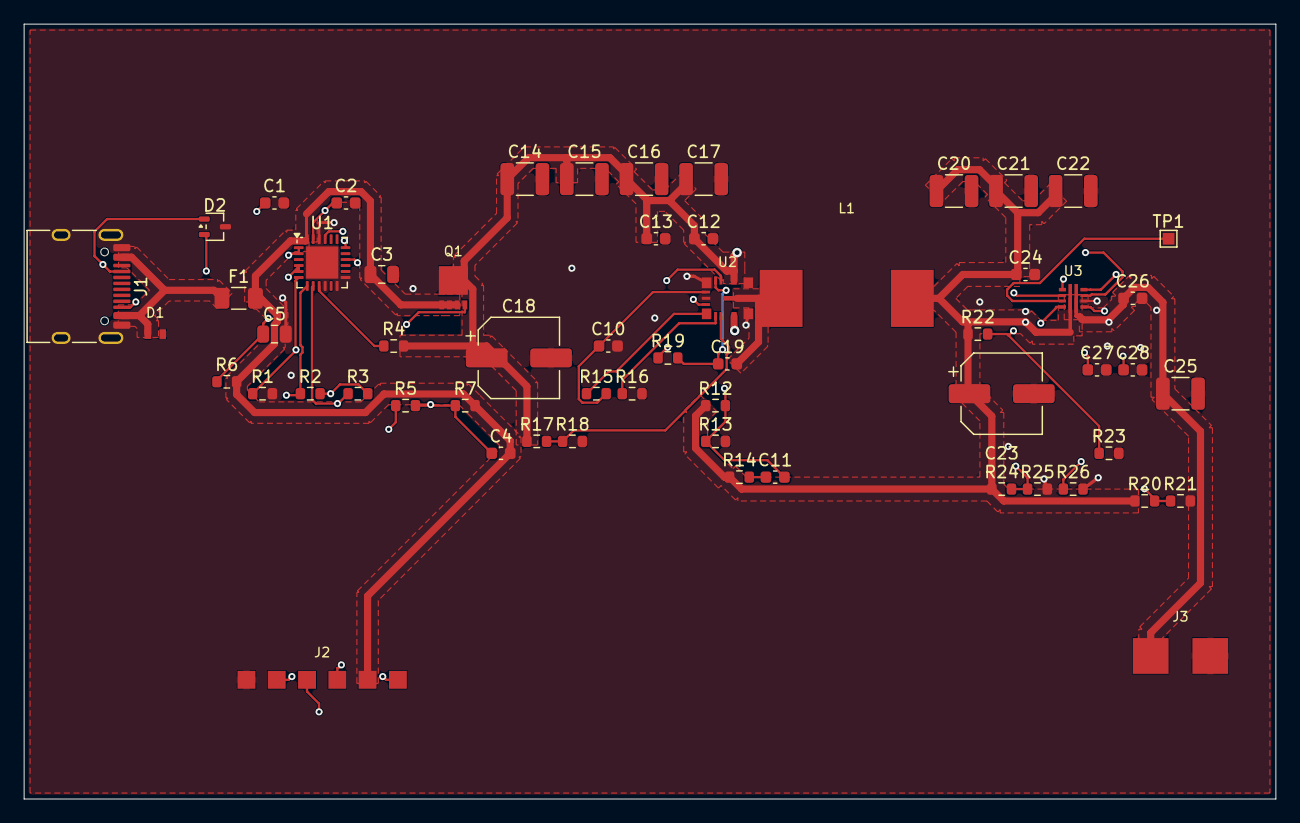
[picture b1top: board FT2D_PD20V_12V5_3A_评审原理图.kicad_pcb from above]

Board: 4 copper layers, 105.0 x 65.0 mm, 58 parts (0 on the bottom side), 33 nets.

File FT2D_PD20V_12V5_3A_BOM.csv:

Designator,Quantity,Manufacturer_Part,Value_or_Requirement,Package_or_Note
J1,1,GCT USB4085-GF-A,USB-C receptacle,KiCad Connector_USB:USB_C_Receptacle_GCT_USB4085; check GF-A drawing
J2,1,Programming test pads,6 pads,2.7 V logic only
J3,1,Two large solder pads,Output cable,Use verified Yaesu E-DC-6 pigtail
TP1,1,Generic test pad,PG diagnostic,1.0x1.0 mm pad
F1,1,Littelfuse 1206SFS300F/32,3 A slow-blow 32 V,1206 check startup surge and thermal derating
U1,1,STUSB4500QTR,USB PD sink,QFN-24 EP 4x4; NVM programming mandatory
Q1,1,STL6P3LLH6,30 V P-MOSFET,PowerFLAT 3.3x3.3
U2,1,LM61460AASQRJRRQ1,6 A buck auto mode spread-spectrum,VQFN-HR RJR 4x3.5 mm
L1,1,Bourns SRP1238A-100M,10 uH 14 A Isat 7 A Irms,13.5x12.5 mm recommended pad
U3,1,TPS259474ARPWR,Circuit-breaker eFuse,QFN RPW 2x2 10 pin auto-retry
D1,1,ESDA25P35-1U1M,VBUS ESD,QFN-2L pinout from ST datasheet
D2,1,ESDA25W,CC1/CC2 ESD,SOT-323 pinout from ST datasheet
R1,1,Generic 0603,10 kohm 1%,RESET pulldown
R2 R3,2,Generic 0603,4.7 kohm 1%,I2C pullup to PD_2V7
R4,1,Generic 0603,1 kohm 1%,VBUS_SW discharge series
R5,1,Generic 0603,22 kohm 1%,PMOS gate series
R6,1,Generic 0603,470 ohm 1%,STUSB VBUS sense series
R7,1,Generic 0603,100 kohm 1%,PMOS gate-to-source
R12,1,Generic 0603,100 kohm 0.1%,Buck FB upper
R13,1,Generic 0603,8.66 kohm 0.1%,Buck FB lower
R14,1,Generic 0603,1 kohm 1%,DNP feedforward tuning
R15,1,Generic 0603,100 kohm 1%,Buck PGOOD pullup
R16,1,Generic 0603,33.2 kohm 1%,400 kHz RT
R17,1,Generic 0603,133 kohm 1%,Buck input UVLO upper
R18,1,Generic 0603,10 kohm 1%,Buck input UVLO lower
R19,1,Generic 0603,0 ohm,Boot rise-time tuning position
R20,1,Generic 0603,470 kohm 1%,eFuse EN upper
R21,1,Generic 0603,100 kohm 1%,eFuse EN lower
R22,1,Generic 0603,101 kohm 1%,eFuse OVLO upper
R23,1,Generic 0603,10 kohm 1%,eFuse OVLO lower
R24,1,Generic 0603,100 kohm 1%,eFuse PGTH upper
R25,1,Generic 0603,12 kohm 1%,eFuse PGTH lower
R26,1,Generic 0603,820 ohm 1%,eFuse ILM about 4.07 A
C1 C2,2,Generic X7R,1 uF 6.3 V,0603 STUSB regulator bypass
C3,1,Generic X7R,1 uF 25 V,0805 STUSB VDD bypass
C4,1,Generic X7R,47 nF 50 V,0603 PMOS gate slew
C5,1,Generic X7R,1 uF 25 V,0603 STUSB VBUS sense filter
C10,1,Generic X7R,1 uF 16 V,0603 Buck VCC bypass
C11,1,Generic C0G,10 pF 50 V,0603 DNP feedforward tuning
C12 C13,2,Generic X7R,100 nF 50 V,0603 Buck VIN/PGND HF bypass
C14 C15 C16 C17,4,Generic X7R,10 uF 50 V,1210 check >=10 uF combined effective at 20 V
C18,1,Panasonic EEHZL1V470R,47 uF 35 V,Hybrid ESR 60 mohm max; 5x5.8 mm
C19,1,Generic X7R,100 nF 16 V,0603 Buck bootstrap
C20 C21 C22,3,Generic X7R,47 uF 25 V,1210/1812 check DC-bias effective capacitance
C23,1,APAQ 250AVHT221M0608,220 uF 25 V,Polymer ESR 24 mohm max; 6.3x7.5 mm
C24,1,Generic X7R,100 nF 25 V,0603 eFuse input bypass
C25,1,Generic X7R,47 uF 25 V,1210/1812 eFuse output bulk
C26,1,Generic X7R,100 nF 25 V,0603 eFuse output HF bypass
C27,1,Generic X7R,3.3 nF 25 V,0603 eFuse dVdt
C28,1,Generic X7R,2.2 nF 10 V,0603 eFuse ITIMER
